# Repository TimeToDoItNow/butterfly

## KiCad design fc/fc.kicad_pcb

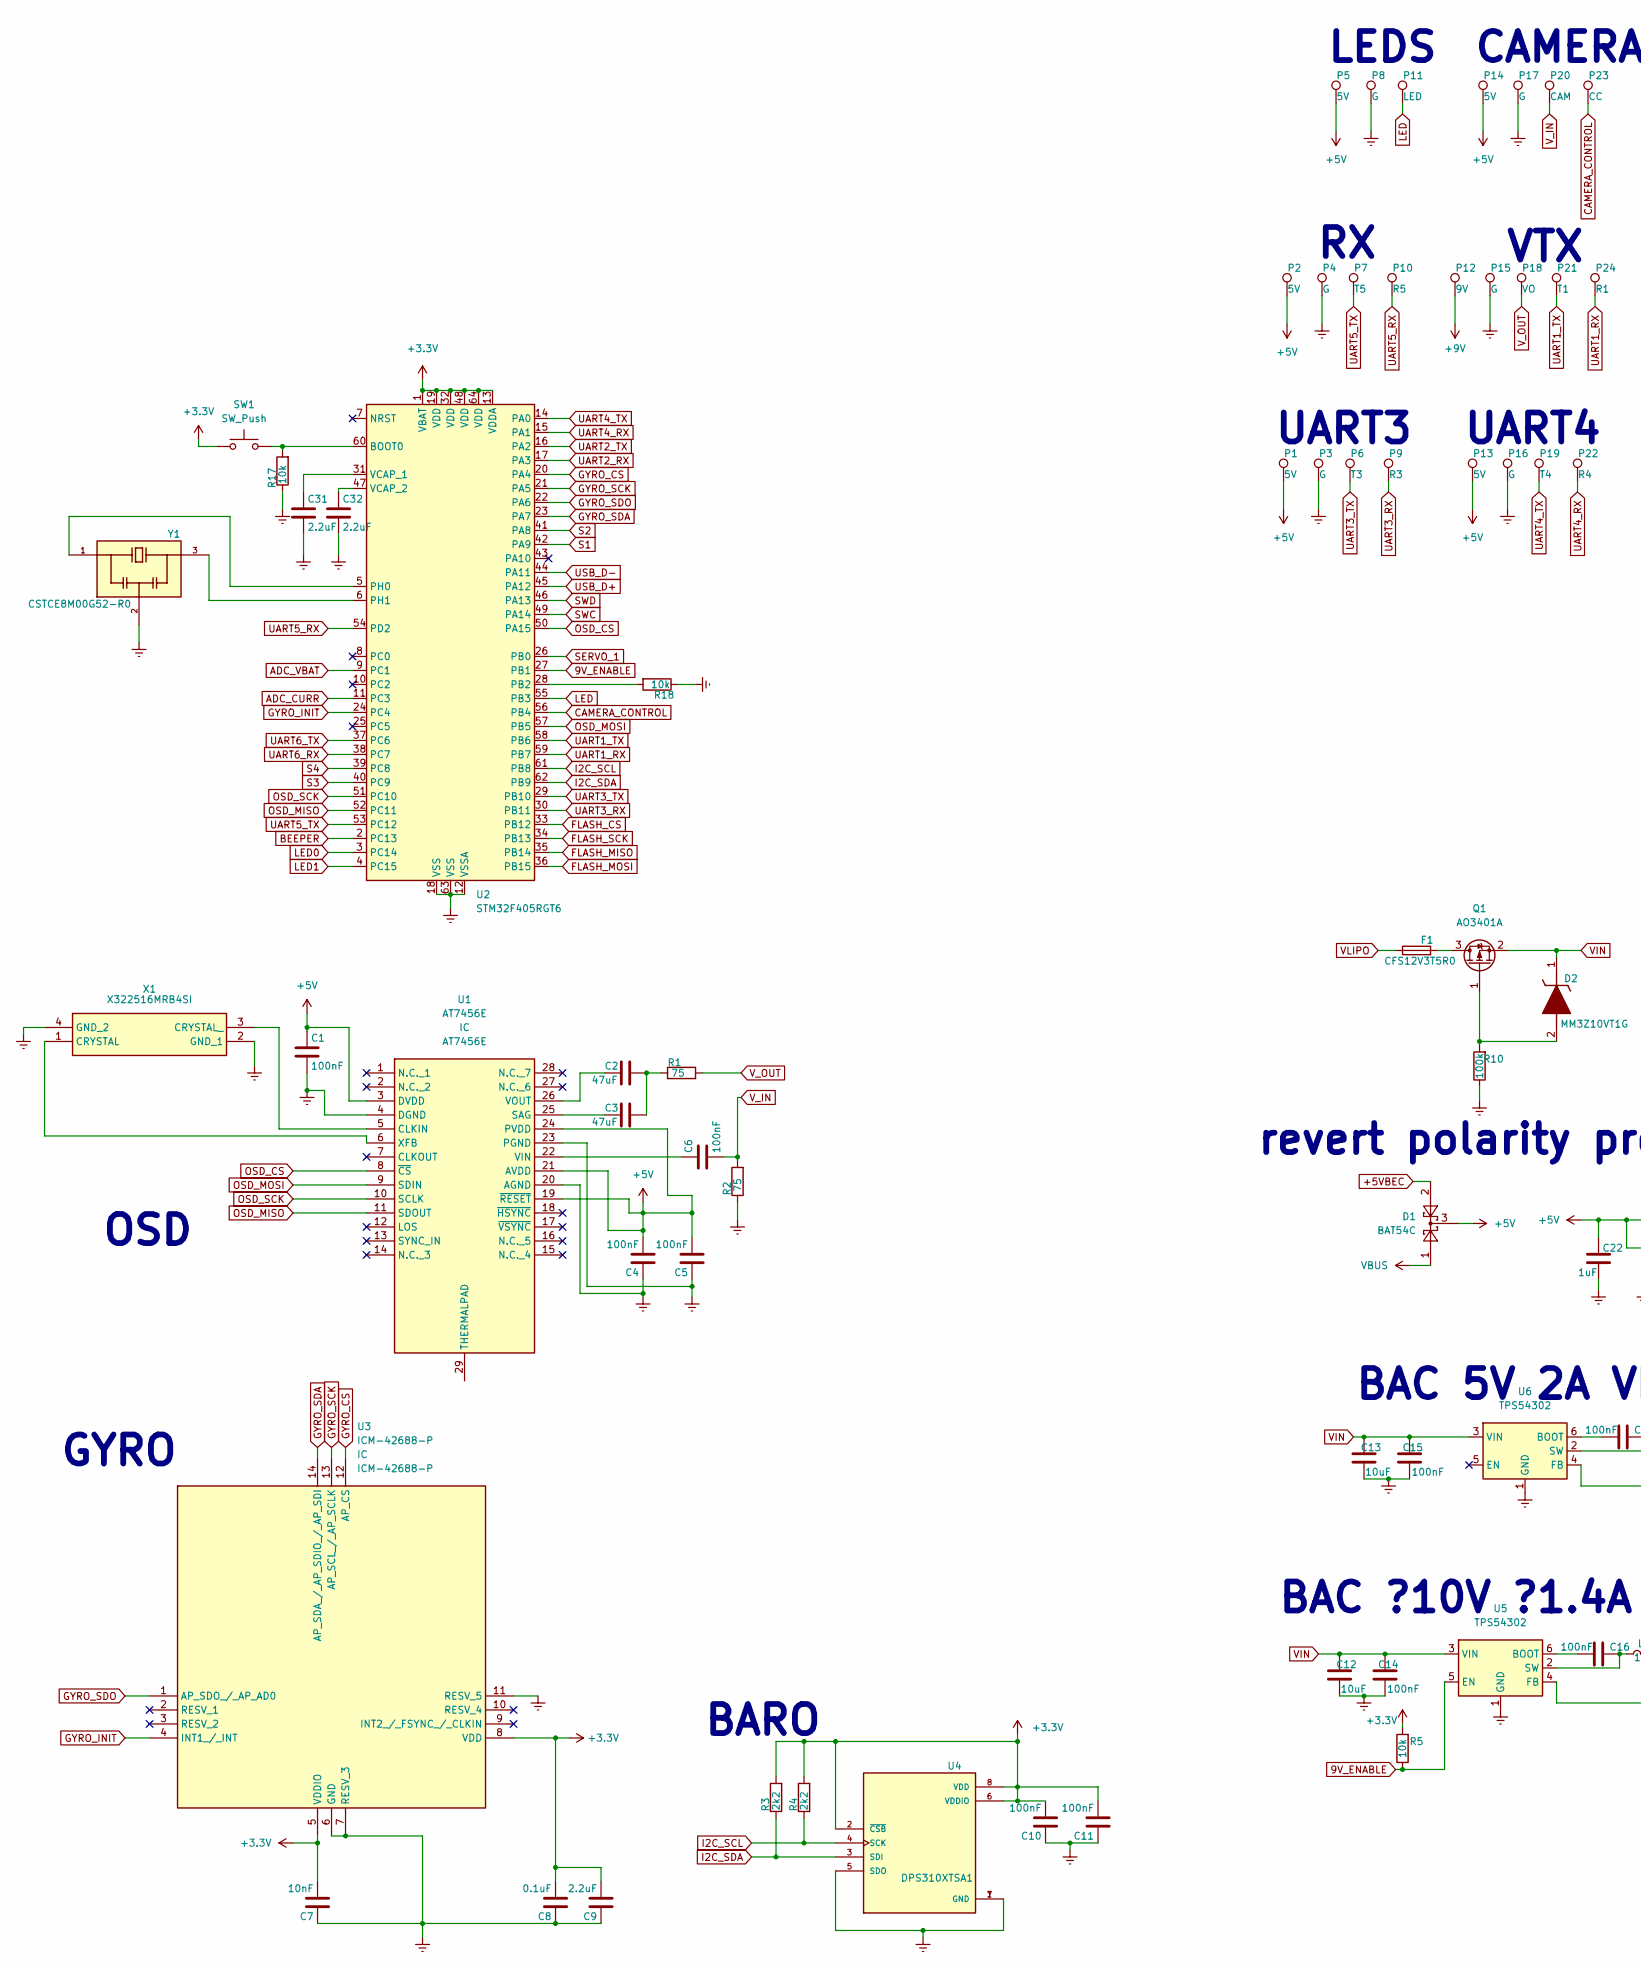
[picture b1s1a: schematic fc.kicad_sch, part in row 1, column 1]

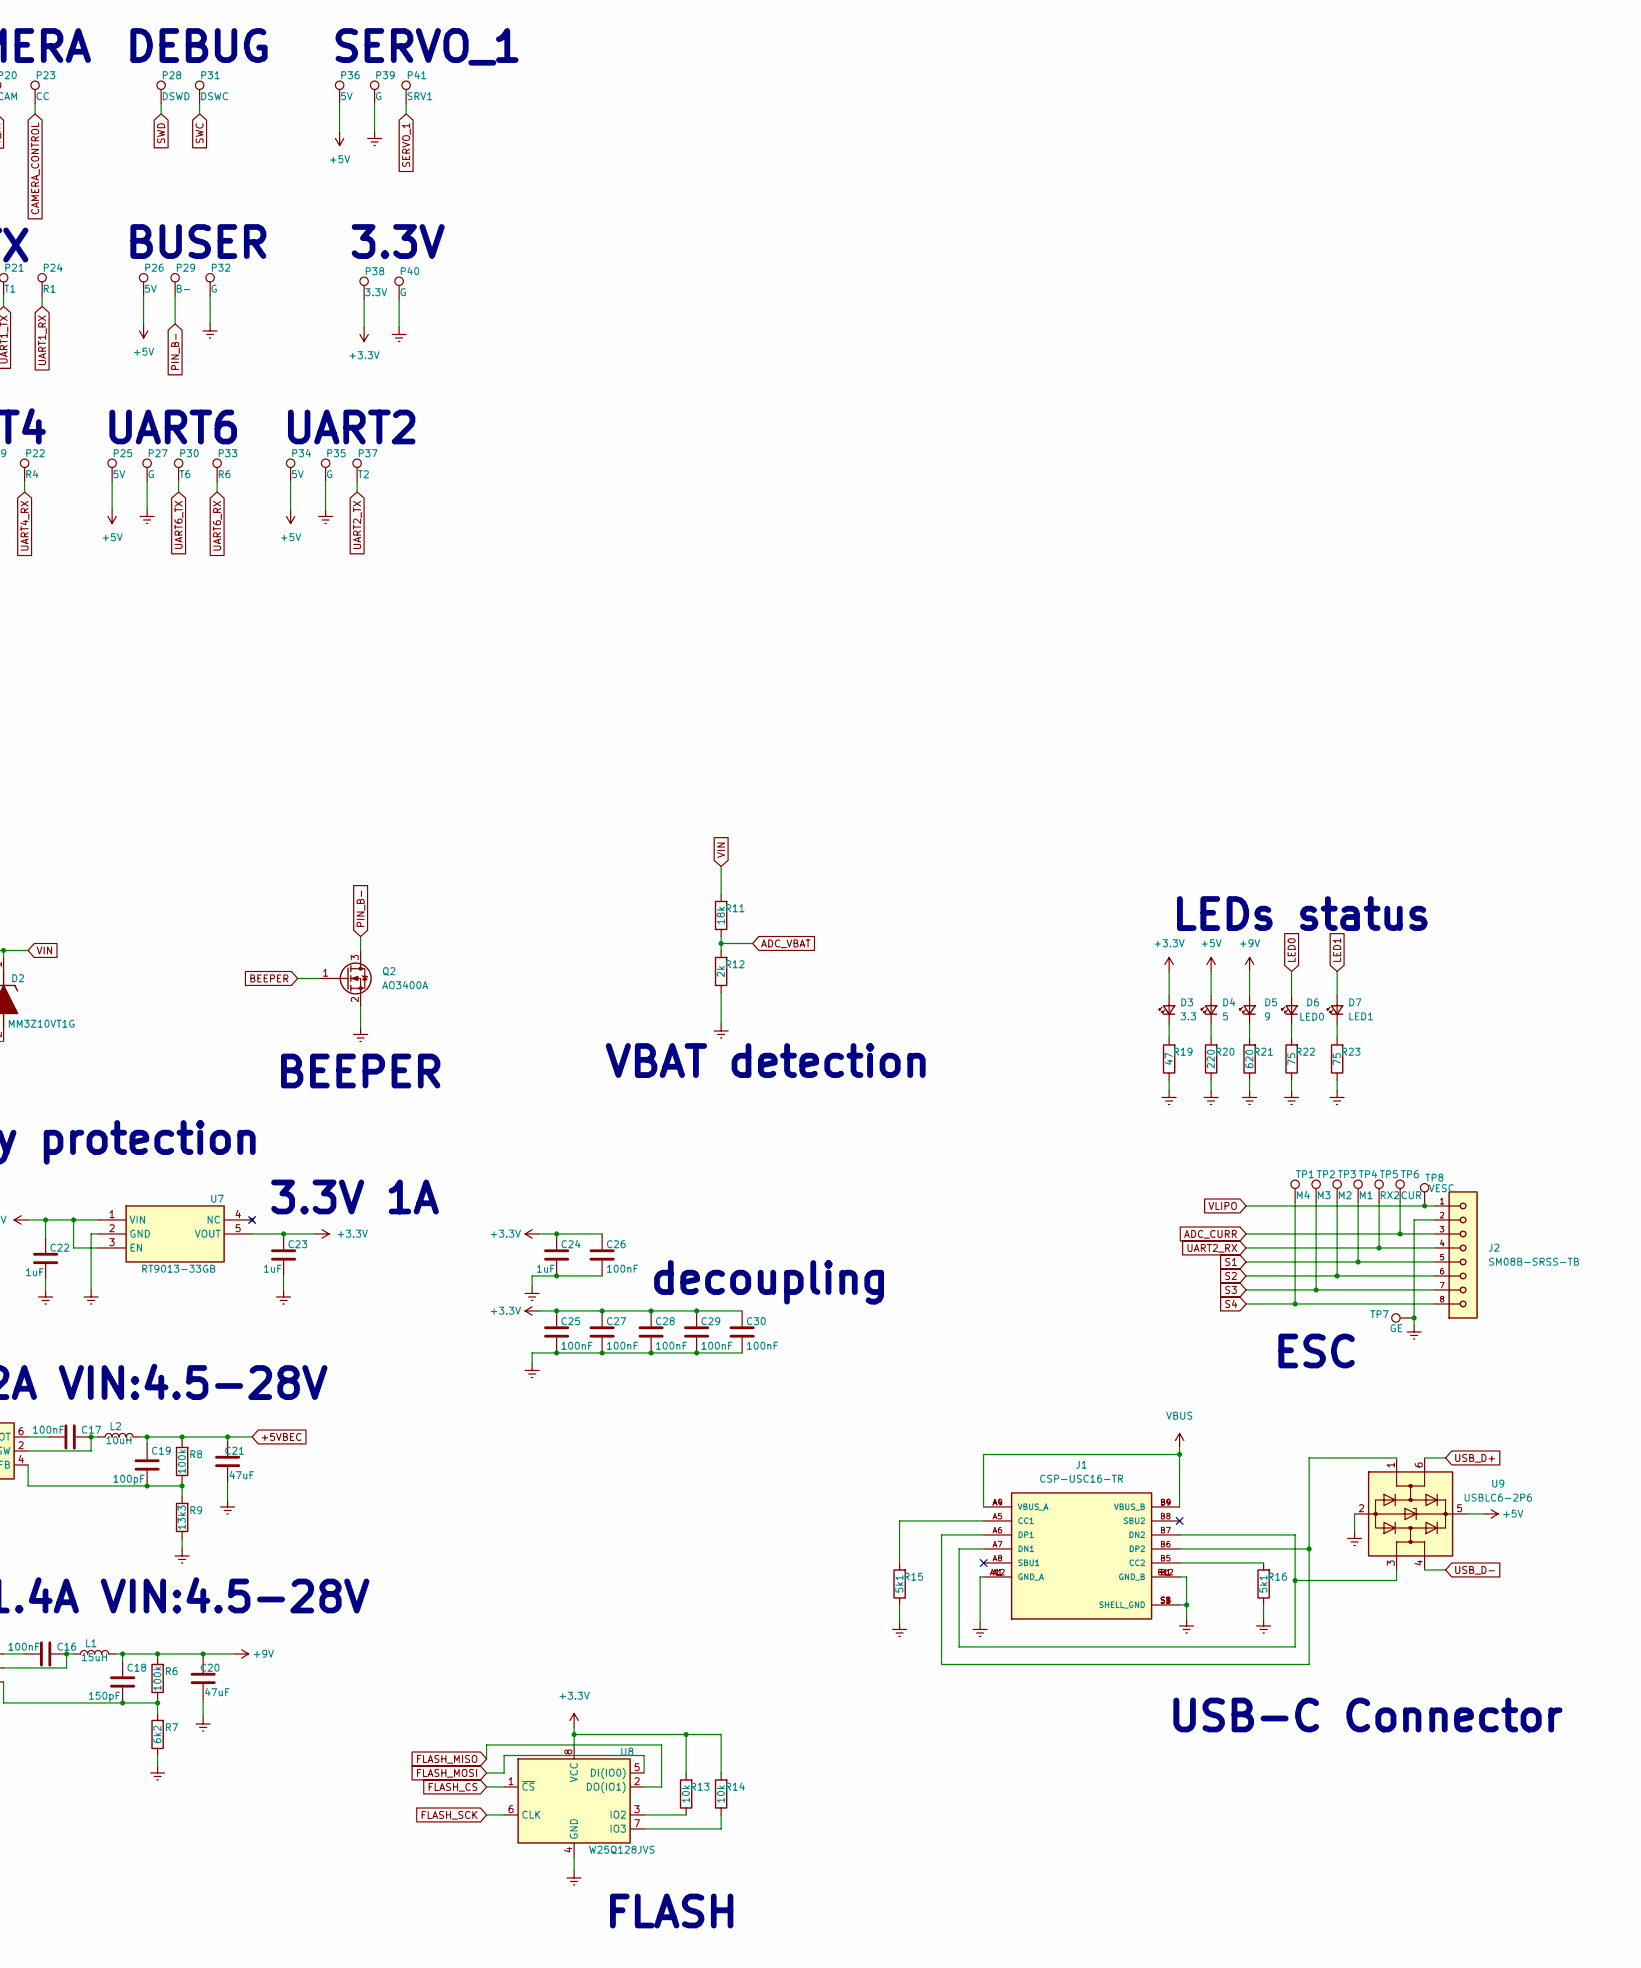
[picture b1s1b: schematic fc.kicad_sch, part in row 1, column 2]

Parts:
C1, C4, C5, C6, C10, C11, C14, C15, C16, C17, C25, C26, C27, C28, C29, C30: 100nF; C_0402_1005Metric
C2, C3, C20, C21: 47uF; C_1206_3216Metric
C7: 10nF; C_0402_1005Metric
C8: 0.1uF; C_0402_1005Metric
C9, C31, C32: 2.2uF; C_0402_1005Metric
C12, C13: 10uF; C_1206_3216Metric
C18: 150pF; C_0603_1608Metric
C19: 100pF; C_0603_1608Metric
C22, C23, C24: 1uF; C_0402_1005Metric
D1: BAT54C; SOT-23
D2: MM3Z10VT1G; SOD2512X110N; Manufacturer_Part_Number MM3Z10VT1G; Mouser Part Number 863-MM3Z10VT1G
D3: 3.3; LED_0603_1608Metric
D4: 5; LED_0603_1608Metric
D5: 9; LED_0603_1608Metric
D6: LED0; LED_0603_1608Metric
D7: LED1; LED_0603_1608Metric
F1: CFS12V3T5R0; Fuse_1206_3216Metric
J1: CSP-USC16-TR; VALCON_CSP-USC16-TR; PARTREV A0
J2: SM08B-SRSS-TB; JST_SM08B-SRSS-TB
L1: 15uH; L7_7_4
L2: 10uH; L7_7_4
P1, P2, P5, P13, P14, P25, P26, P34, P36: 5V; PAD_20_15
P3, P4, P8, P15, P16, P17, P27, P32, P35, P39, P40: G; PAD_20_15
P6: T3; PAD_20_15
P7: T5; PAD_20_15
P9: R3; PAD_20_15
P10: R5; PAD_20_15
P11: LED; PAD_20_15
P12: 9V; PAD_20_15
P18: VO; PAD_20_15
P19: T4; PAD_20_15
P20: CAM; PAD_20_15
P21: T1; PAD_20_15
P22: R4; PAD_20_15
P23: CC; PAD_20_15
P24: R1; PAD_20_15
P28: DSWD; PAD_20_15
P29: B-; PAD_20_15
P30: T6; PAD_20_15
P31: DSWC; PAD_20_15
P33: R6; PAD_20_15
P37: T2; PAD_20_15
P38: 3.3V; PAD_20_15
P41: SRV1; PAD_20_15
Q1: AO3401A; SOT-23
Q2: AO3400A; SOT-23
R1, R2, R22, R23: 75; R_0402_1005Metric
R3, R4: 2k2; R_0402_1005Metric
R5, R13, R14, R17, R18: 10k; R_0402_1005Metric
R6, R8, R10: 100k; R_0402_1005Metric
R7: 6k2; R_0402_1005Metric
R9: 13k3; R_0402_1005Metric
R11: 18k; R_0402_1005Metric
R12: 2k; R_0402_1005Metric
R15, R16: 5k1; R_0402_1005Metric
R19: 47; R_0402_1005Metric
R20: 220; R_0402_1005Metric
R21: 620; R_0402_1005Metric
SW1: SW_Push; SW_DIP_SPSTx01_Slide_6.7x4.1mm_W8.61mm_P2.54mm_LowProfile
TP1: M4; TPOINT
TP2: M3; TPOINT
TP3: M2; TPOINT
TP4: M1; TPOINT
TP5: RX2; TPOINT
TP6: CUR; TPOINT
TP7: GE; TPOINT
TP8: VESC; TPOINT
U1: AT7456E; SOP65P640X120-29N; Manufacturer_Part_Number AT7456E
U2: STM32F405RGT6; LQFP-64_10x10mm_P0.5mm
U3: ICM-42688-P; Manufacturer_Part_Number ICM-42688-P; Mouser Part Number 410-ICM-42688-P
U4: DPS310XTSA1; XDCR_DPS310XTSA1
U5, U6: TPS54302; SOT-23-6
U7: RT9013-33GB; SOT94P279X130-5N; Manufacturer_Part_Number RT9013-33GB; Mouser Part Number 835-RT9013-33GB
U8: W25Q128JVS; SOIC-8_5.23x5.23mm_P1.27mm
U9: USBLC6-2P6; SOT-666
X1: X322516MRB4SI; Manufacturer_Part_Number X322516MRB4SI
Y1: CSTCE8M00G52-R0; OSC_CSTCE8M00G52-R0; PARTREV May 7, 2019

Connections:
9V_ENABLE: R5.1, U2.27 (PB1), U5.5 (EN)
+3.3V: C7.2, C8.2, C9.2, C10.2, C11.2, C23.1, C24.1, C25.1, C26.1, C27.1, C28.1, C29.1, C30.1, D3.2 (A), P38.1, R3.2, R4.2, R5.2, R13.2, R14.2, SW1.1, U2.1 (VBAT), U2.13 (VDDA), U2.19 (VDD), U2.32 (VDD), U2.48 (VDD), U2.64 (VDD), U3.5 (VDDIO), U3.8 (VDD), U4.2 (~CSB), U4.6 (VDDIO), U4.8 (VDD), U7.5 (VOUT), U8.8 (VCC)
+5V: C1.1, C4.2, C5.2, C22.1, D1.3, D4.2 (A), P1.1, P2.1, P5.1, P13.1, P14.1, P25.1, P26.1, P34.1, P36.1, U1.3 (DVDD), U1.19 (~RESET), U1.21 (AVDD), U1.24 (PVDD), U7.1 (VIN), U7.3 (EN), U9.5 (VBUS)
+5VBEC: C19.1, C21.2, D1.2, L2.2, R8.2
+9V: C18.1, C20.2, D5.2 (A), L1.2, P12.1, R6.2
ADC_CURR: J2.3, TP6.1, U2.11 (PC3)
ADC_VBAT: R11.1, R12.2, U2.9 (PC1)
BEEPER: Q2.1 (G), U2.2 (PC13)
CAMERA_CONTROL: P23.1, U2.56 (PB4)
Earth: C1.2, C4.1, C5.1, C7.1, C8.1, C9.1, C10.1, C11.1, C12.1, C13.1, C14.1, C15.1, C20.1, C21.1, C22.2, C23.2, C24.2, C25.2, C26.2, C27.2, C28.2, C29.2, C30.2, C31.2, C32.2, J1.A1 (GND_A), J1.A12 (GND_A), J1.B1 (GND_B), J1.B12 (GND_B), J1.S1 (SHELL_GND), J1.S2 (SHELL_GND), J1.S3 (SHELL_GND), J1.S4 (SHELL_GND), J2.2, J2.P1, J2.P2, P3.1, P4.1, P8.1, P15.1, P16.1, P17.1, P27.1, P32.1, P35.1, P39.1, P40.1, Q2.2 (S), R2.1, R7.1, R9.1, R10.1, R12.1, R15.1, R16.1, R17.1, R18.1, R19.1, R20.1, R21.1, R22.1, R23.1, TP7.1, U1.4 (DGND), U1.20 (AGND), U1.23 (PGND), U1.29 (THERMALPAD), U2.12 (VSSA), U2.18 (VSS), U2.63 (VSS), U3.6 (GND), U3.7 (RESV_3), U3.11 (RESV_5), U4.1 (GND), U4.5 (SDO), U4.7 (GND), U5.1 (GND), U6.1 (GND), U7.2 (GND), U8.4 (GND), U9.2 (GND), X1.2 (GND_1), X1.4 (GND_2), Y1.2
FLASH_CS: U2.33 (PB12), U8.1 (~CS)
FLASH_MISO: U2.35 (PB14), U8.2 (DO(IO1))
FLASH_MOSI: U2.36 (PB15), U8.5 (DI(IO0))
FLASH_SCK: U2.34 (PB13), U8.6 (CLK)
GYRO_CS: U2.20 (PA4), U3.12 (AP_CS)
GYRO_INIT: U2.24 (PC4), U3.4 (INT1_/_INT)
GYRO_SCK: U2.21 (PA5), U3.13 (AP_SCL_/_AP_SCLK)
GYRO_SDA: U2.23 (PA7), U3.14 (AP_SDA_/_AP_SDIO_/_AP_SDI)
GYRO_SDO: U2.22 (PA6), U3.1 (AP_SDO_/_AP_AD0)
I2C_SCL: R4.1, U2.61 (PB8), U4.4 (SCK)
I2C_SDA: R3.1, U2.62 (PB9), U4.3 (SDI)
LED: P11.1, U2.55 (PB3)
LED0: D6.2 (A), U2.3 (PC14)
LED1: D7.2 (A), U2.4 (PC15)
unnamed: C2.1, U1.26 (VOUT)
unnamed: C2.2, C3.2, R1.1
unnamed: C3.1, U1.25 (SAG)
unnamed: C6.1, U1.22 (VIN)
unnamed: C16.1, L1.1, U5.2 (SW)
unnamed: C16.2, U5.6 (BOOT)
unnamed: C17.1, L2.1, U6.2 (SW)
unnamed: C17.2, U6.6 (BOOT)
unnamed: C18.2, R6.1, R7.2, U5.4 (FB)
unnamed: C19.2, R8.1, R9.2, U6.4 (FB)
unnamed: C31.1, U2.31 (VCAP_1)
unnamed: C32.1, U2.47 (VCAP_2)
unnamed: D2.2 (A), Q1.1 (G), R10.2
unnamed: D3.1 (K), R19.2
unnamed: D4.1 (K), R20.2
unnamed: D5.1 (K), R21.2
unnamed: D6.1 (K), R22.2
unnamed: D7.1 (K), R23.2
unnamed: F1.2, Q1.3 (D)
unnamed: J1.A5 (CC1), R15.2
unnamed: J1.A6 (DP1), J1.B6 (DP2), U9.1 (I/O1)
unnamed: J1.A7 (DN1), J1.B7 (DN2), U9.3 (I/O2)
unnamed: J1.B5 (CC2), R16.2
unnamed: R13.1, U8.3 (IO2)
unnamed: R14.1, U8.7 (IO3)
unnamed: R17.2, SW1.2, U2.60 (BOOT0)
unnamed: R18.2, U2.28 (PB2)
unnamed: U1.5 (CLKIN), X1.3 (CRYSTAL_)
unnamed: U1.6 (XFB), X1.1 (CRYSTAL)
unnamed: U2.5 (PH0), Y1.1
unnamed: U2.6 (PH1), Y1.3
OSD_CS: U1.8 (~CS), U2.50 (PA15)
OSD_MISO: U1.11 (SDOUT), U2.52 (PC11)
OSD_MOSI: U1.9 (SDIN), U2.57 (PB5)
OSD_SCK: U1.10 (SCLK), U2.51 (PC10)
PIN_B-: P29.1, Q2.3 (D)
S1: J2.5, TP4.1, U2.42 (PA9)
S2: J2.6, TP3.1, U2.41 (PA8)
S3: J2.7, TP2.1, U2.40 (PC9)
S4: J2.8, TP1.1, U2.39 (PC8)
SERVO_1: P41.1, U2.26 (PB0)
SWC: P31.1, U2.49 (PA14)
SWD: P28.1, U2.46 (PA13)
UART1_RX: P24.1, U2.59 (PB7)
UART1_TX: P21.1, U2.58 (PB6)
UART2_RX: J2.4, TP5.1, U2.17 (PA3)
UART2_TX: P37.1, U2.16 (PA2)
UART3_RX: P9.1, U2.30 (PB11)
UART3_TX: P6.1, U2.29 (PB10)
UART4_RX: P22.1, U2.15 (PA1)
UART4_TX: P19.1, U2.14 (PA0)
UART5_RX: P10.1, U2.54 (PD2)
UART5_TX: P7.1, U2.53 (PC12)
UART6_RX: P33.1, U2.38 (PC7)
UART6_TX: P30.1, U2.37 (PC6)
USB_D+: U2.45 (PA12), U9.6 (I/O1)
USB_D-: U2.44 (PA11), U9.4 (I/O2)
VBUS: D1.1, J1.A4 (VBUS_A), J1.A9 (VBUS_A), J1.B4 (VBUS_B), J1.B9 (VBUS_B)
VIN: C12.2, C13.2, C14.2, C15.2, D2.1 (K), Q1.2 (S), R11.2, U5.3 (VIN), U6.3 (VIN)
VLIPO: F1.1, J2.1, TP8.1
V_IN: C6.2, P20.1, R2.2
V_OUT: P18.1, R1.2

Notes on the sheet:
UART3
revert polarity protection
ESC
UART4
GYRO
VBAT detection
OSD
BUSER
3.3V 1A
FLASH
BAC 5V 2A VIN:4.5-28V
DEBUG
LEDS
UART6
BAC ?10V ?1.4A VIN:4.5-28V
USB-C Connector
decoupling
BEEPER
CAMERA
UART2
LEDs status
SERVO_1
BARO
3.3V
VTX

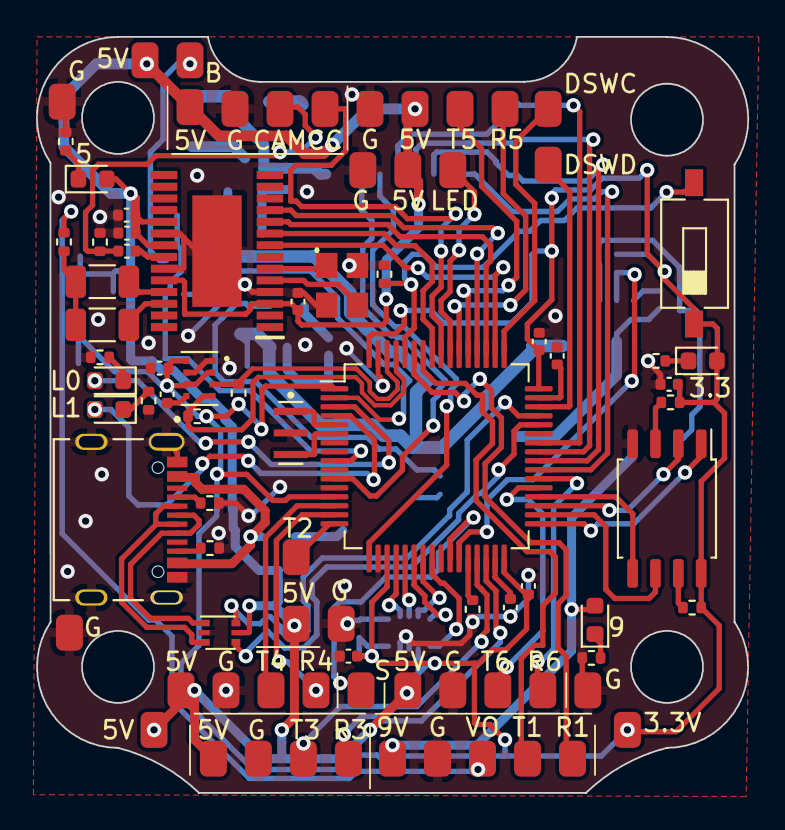
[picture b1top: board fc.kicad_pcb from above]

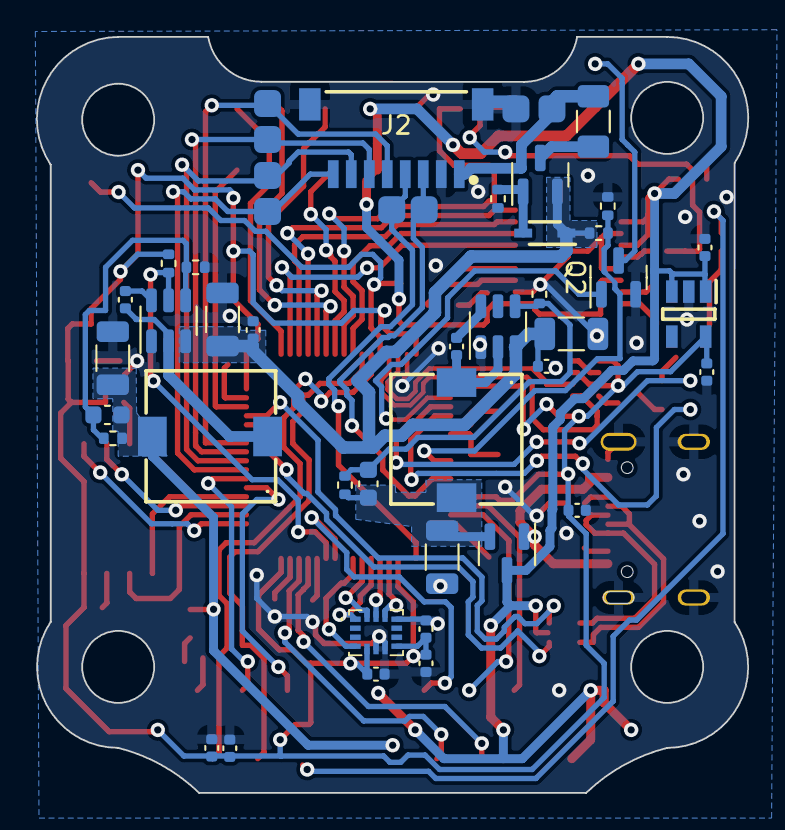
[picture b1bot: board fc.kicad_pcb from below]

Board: 2 copper layers, 39.5 x 42.0 mm, 130 parts (46 on the bottom side), 86 nets.
